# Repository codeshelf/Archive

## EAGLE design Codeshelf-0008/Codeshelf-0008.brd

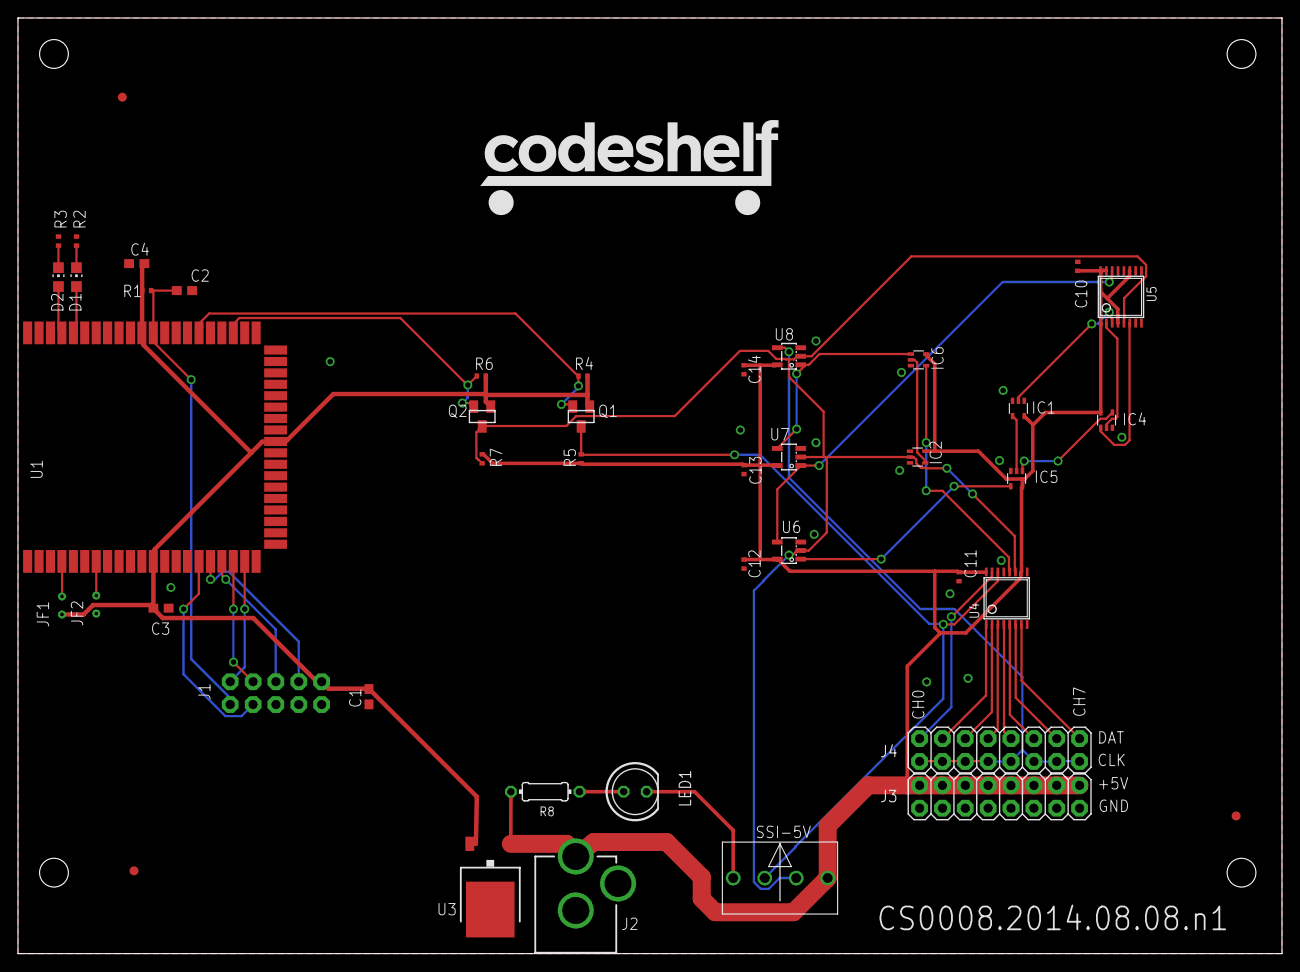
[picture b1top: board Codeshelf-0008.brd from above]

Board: 2 copper layers, 140.5 x 104.0 mm, 45 parts (1 on the bottom side), 39 nets.

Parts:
C1, C3, C4: 100pF; C0603
C2: 1nF; C0603
C10, C11, C12, C13, C14: .1uF; C0402
D1: RED; CHIP-LED0805
D2: GREEN; CHIP-LED0805
IC1, IC2: 74AHC1G04DCK; SC70-5
IC4, IC5, IC6: 74AHC1G08DCK; SC70-5
J1: M05X2PTH; AVR_ICSP
J2: POWER_JACKPTH; POWER_JACK_PTH
J3, J4: M08X2; 2X8
JF1, JF2: JUMPER-2X-SMT-VIA; JUMPER-VIA-2X
LED1: BLUE; LED5MM
Q1, Q2: MOSFET-NCHANNELBSS138; SOT23
R1: 100K; RF-R0402
R2: 220; RF-R0402
R3: 390; RF-R0402
R4, R5, R6, R7: 10K; RF-R0402
R8: 1K; 0204/7
SSI-5V: HEADER-4X39357; MOLEX-39357-0004
U1: ZSFM201-1A; ZSFM201-1
U3: LM2936DT-3.3; TO252
U4: SN74HC595PW; TSSOP16
U5: 74HCT193PW; TSSOP16
U6, U7, U8: D-FLIP-FLOP-74LV1G79DBVR; SOT23-5
U$1: CODESHELF-LOGO
U$2, U$3, U$4: FIDUCIAL; FIDUCIAL_1MM

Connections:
+3V3: C1.1, C3.2, C4.2, J1.9, JF1.1, Q1.1, Q2.1, R1.2, R4.1, R6.1, U1.12, U1.31, U1.50, U3.2
+5V: C10.1, C11.2, C12.2, C13.2, C14.2, IC1.5, IC2.5, IC4.5, IC5.5, IC6.5, J2.PWR, J3.1, J3.3, J3.5, J3.7, J3.9, J3.11, J3.13, J3.15, R5.1, R7.1, R8.2, SSI-5V.4, U3.1, U4.10, U4.16, U5.1, U5.4, U5.11, U5.15, U5.16, U6.5, U7.5, U8.5
GND: C1.2, C2.2, C3.1, C4.1, C10.2, C11.1, C12.1, C13.1, C14.1, IC1.3, IC2.3, IC4.3, IC5.3, IC6.3, J1.10, J2.GND, J2.GNDBREAK, J3.2, J3.4, J3.6, J3.8, J3.10, J3.12, J3.14, J3.16, JF2.1, LED1.K, R2.1, R3.1, SSI-5V.1, U1.1, U1.2, U1.3, U1.22, U1.38, U1.51, U1.58, U1.59, U1.60, U3.3, U4.8, U4.13, U5.8, U6.3, U7.3, U8.3
unnamed: D2.A, U1.57
unnamed: D1.A, U1.56
unnamed: D2.C, R3.2
unnamed: D1.C, R2.2
unnamed: LED1.A, R8.1
unnamed: JF2.2, U1.7
unnamed: JF1.2, U1.4
unnamed: J4.13, U4.1
unnamed: J4.11, U4.2
unnamed: J4.9, U4.3
unnamed: J4.7, U4.4
unnamed: J4.5, U4.5
unnamed: J4.3, U4.6
unnamed: J4.1, U4.7
unnamed: J4.15, U4.15
unnamed: IC1.4, IC5.2
unnamed: IC4.4, IC5.1
unnamed: IC5.4, U6.1
unnamed: U5.14, U6.4, U7.1
unnamed: IC6.1, U7.4, U8.1
unnamed: IC2.4, IC6.2
unnamed: IC1.2, U5.3
unnamed: IC4.2, U5.2
unnamed: IC4.1, U5.6
unnamed: IC6.4, U4.12
RESET: C2.1, J1.2, R1.1, U1.49
RTCK: J1.4, U1.16
SSI-CLK: J4.2, J4.4, J4.6, J4.8, J4.10, J4.12, J4.14, J4.16, U8.4
SSI-CLK-3V3: Q2.2, R6.2, U1.42
SSI-CLK-5V: IC2.2, Q2.3, R7.2, SSI-5V.3, U4.11, U5.5, U6.2, U7.2, U8.2
SSI-TX-3V3: Q1.2, R4.2, U1.45
SSI-TX-5V: Q1.3, R5.2, SSI-5V.2, U4.14
TCK: J1.3, U1.19
TDI: J1.5, U1.18
TDO: J1.7, U1.17
TMS: J1.1, U1.20

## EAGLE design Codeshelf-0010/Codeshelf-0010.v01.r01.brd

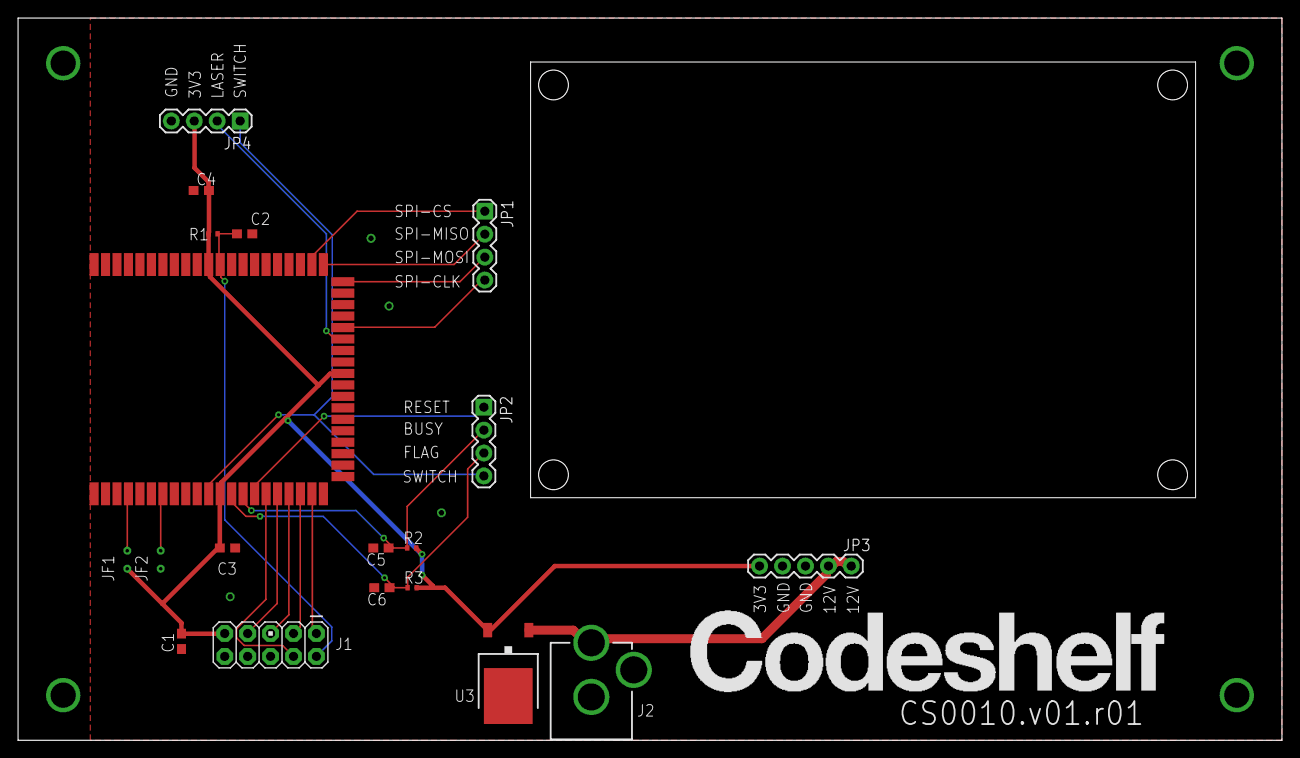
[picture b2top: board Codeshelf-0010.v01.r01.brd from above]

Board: 2 copper layers, 140.0 x 80.0 mm, 21 parts (0 on the bottom side), 20 nets.

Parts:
C1, C3, C4: 100pF; C0603
C2, C5, C6: 1nF; C0603
J1: M05X2PTH; AVR_ICSP
J2: POWER_JACKPTH; POWER_JACK_PTH
JF1, JF2: JUMPER-2X-SMT-VIA; JUMPER-VIA-2X
JP1, JP2, JP4: 1X04
JP3: 1X05
LOGO: CODESHELF-LOGO
R1, R2, R3: 100K; RF-R0402
U1: ZSFM201-1A; ZSFM201-1
U3: LM2936DT-3.3; TO252
U$1: SPARKFUN-BOB-11611

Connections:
#BUSY: C5.1, JP2.2, R2.1, U1.14
#FLAG: C6.1, JP2.3, R3.1, U1.13
#RESET: JP2.1, U1.15
+3V3: C1.1, C3.2, C4.2, J1.9, JF1.1, JP3.5, JP4.3, R1.2, R2.2, R3.2, U1.12, U1.31, U1.50, U3.2
+12V: J2.PWR, JP3.1, JP3.2, U3.1
GND: C1.2, C2.2, C3.1, C4.1, C5.2, C6.2, J1.10, J2.GND, J2.GNDBREAK, JF2.1, JP3.3, JP3.4, JP4.4, U1.1, U1.2, U1.3, U1.22, U1.38, U1.51, U1.58, U1.59, U1.60, U3.3
LASER: JP4.2, U1.34
unnamed: JF2.2, U1.7
unnamed: JF1.2, U1.4
RESET: C2.1, J1.2, R1.1, U1.49
RTCK: J1.4, U1.16
SPI_CLK: JP1.4, U1.35
SPI_CS: JP1.1, U1.41
SPI_MISO: JP1.2, U1.40
SPI_MOSI: JP1.3, U1.39
SWITCH: JP2.4, JP4.1, U1.11
TCK: J1.3, U1.19
TDI: J1.5, U1.18
TDO: J1.7, U1.17
TMS: J1.1, U1.20

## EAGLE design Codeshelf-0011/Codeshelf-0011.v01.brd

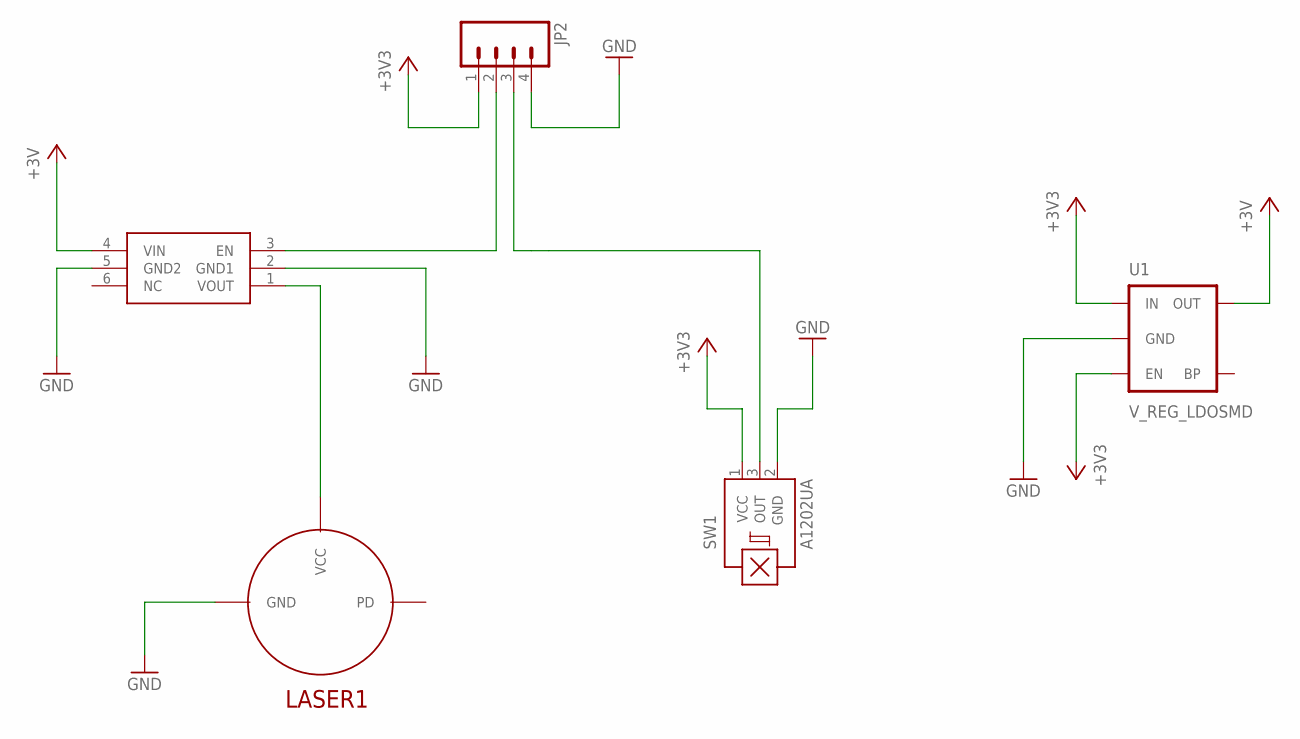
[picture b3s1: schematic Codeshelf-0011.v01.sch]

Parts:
JP2: M04PTH; 1X04
LASER1: LMAPCD-650-06
SW1: A1202UA; SIP3-UA
U1: V_REG_LDOSMD; SOT23-5
U2: MIC94061C6; SC70-6L

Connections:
+3V: U1.5 (OUT), U2.4 (VIN)
+3V3: JP2.1, SW1.1 (VCC), U1.1 (IN), U1.3 (EN)
GND: JP2.4, LASER1.1 (GND), SW1.2 (GND), U1.2 (GND), U2.2 (GND1), U2.5 (GND2)
unnamed: JP2.2, U2.3 (EN)
unnamed: JP2.3, SW1.3 (OUT)
VCC: LASER1.2 (VCC), U2.1 (VOUT)

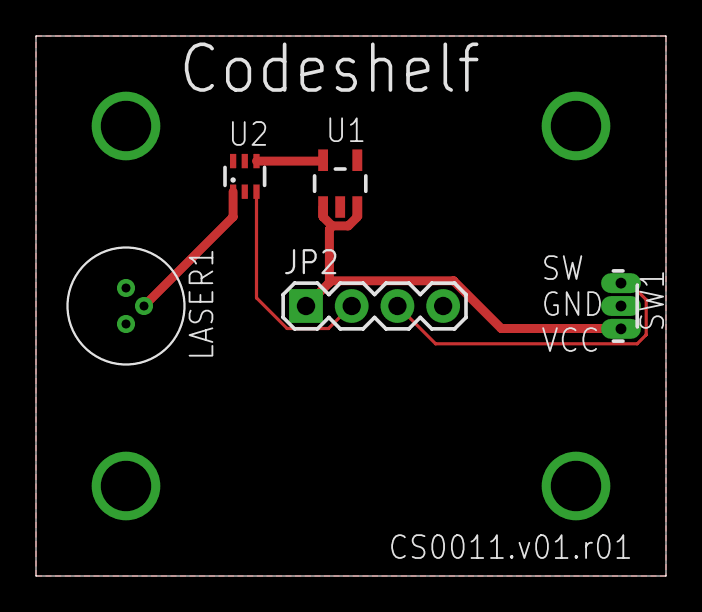
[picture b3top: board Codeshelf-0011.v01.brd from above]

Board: 2 copper layers, 35.0 x 30.0 mm, 5 parts (0 on the bottom side), 6 nets.

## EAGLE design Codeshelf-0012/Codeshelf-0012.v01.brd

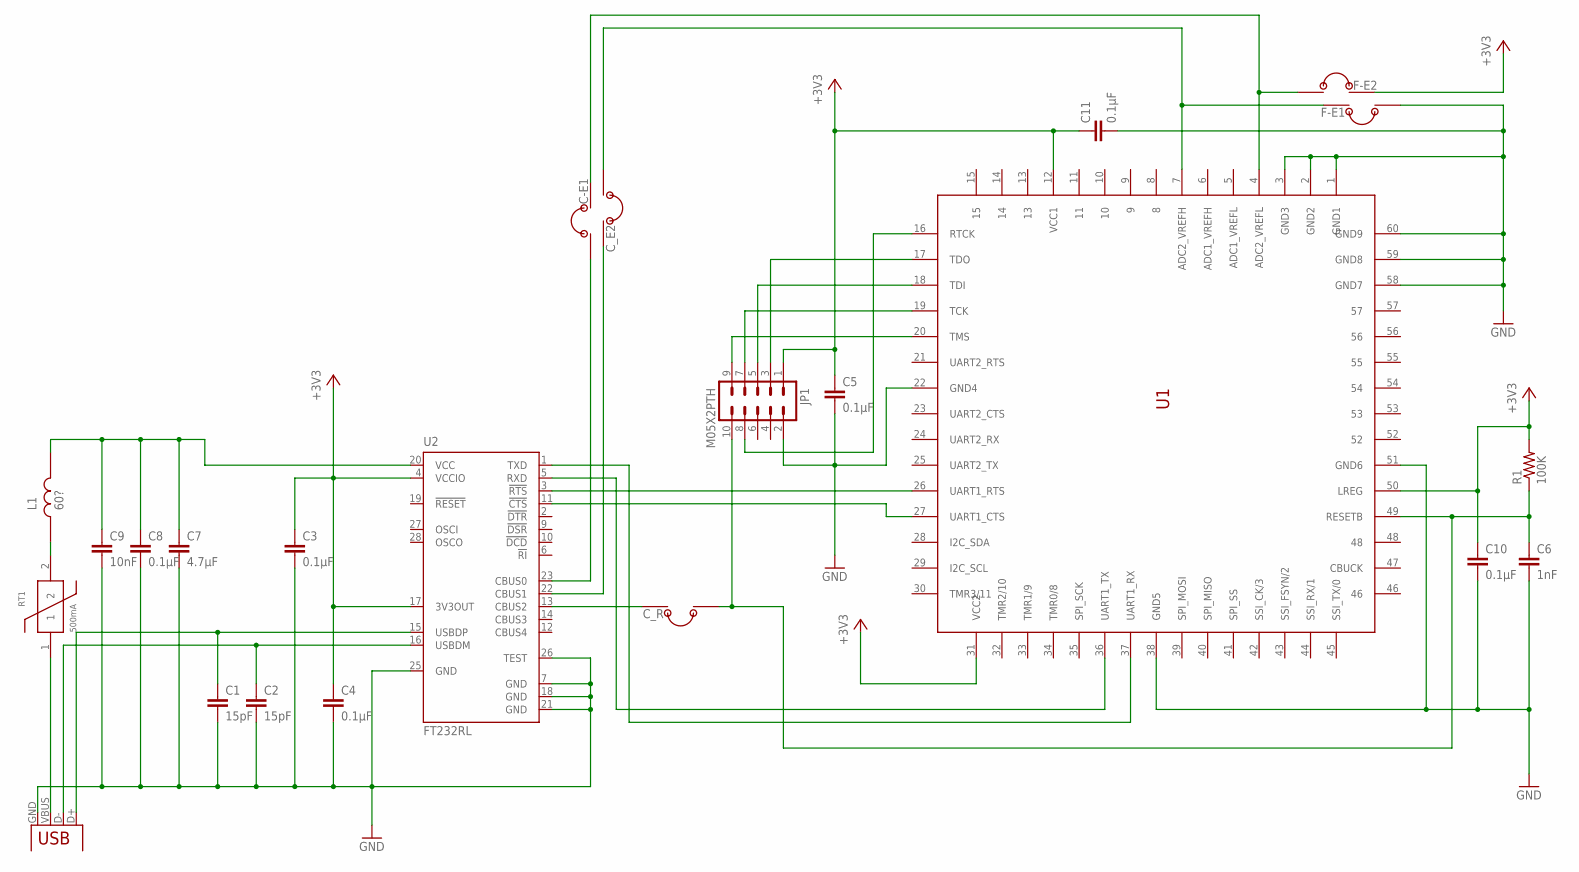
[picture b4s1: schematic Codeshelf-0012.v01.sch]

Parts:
C1, C2: 15pF; C0402
C3, C4, C5, C8, C10, C11: 0.1µF; C0402
C6: 1nF; C0402
C7: 4.7µF; C0805
C9: 10nF; C0402
C-E1: JUMPER-2X-SMT-VIA; JUMPER-VIA-2X
C_E2: JUMPER-2X-SMT-VIA; JUMPER-VIA-2X
C_R: JUMPER-2X-SMT-VIA; JUMPER-VIA-2X
F-E1, F-E2: JUMPER-2X-SMT-VIA; JUMPER-VIA-2X
JP1: M05X2PTH; AVR_ICSP
L1: 60?; RF-L0603
R1: 100K; RF-R0402
RT1: 500mA; C1210
U1: ZSFM201-1A; ZSFM201-1
U2: FT232RL; SSOP28
X1: USBPTH; USB-B-PTH

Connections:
+3V3: C3.1, C4.1, C5.1, C10.1, C11.1, F-E2.2, JP1.1, R1.2, U1.12 (VCC1), U1.31 (VCC2), U1.50 (LREG), U2.4 (VCCIO), U2.17 (3V3OUT)
GND: C1.2, C2.2, C3.2, C4.2, C5.2, C6.2, C7.2, C8.2, C9.2, C10.2, C11.2, F-E1.1, JP1.2, U1.1 (GND1), U1.2 (GND2), U1.3 (GND3), U1.22 (GND4), U1.38 (GND5), U1.51 (GND6), U1.58 (GND7), U1.59 (GND8), U1.60 (GND9), U2.7 (GND), U2.18 (GND), U2.21 (GND), U2.25 (GND), U2.26 (TEST), X1.GND
MCU_CTS: U1.27 (UART1_CTS), U2.11 (!CTS)
MCU_RTS: U1.26 (UART1_RTS), U2.3 (!RTS)
MCU_RX: U1.37 (UART1_RX), U2.1 (TXD)
MCU_TX: U1.36 (UART1_TX), U2.5 (RXD)
unnamed: C-E1.2, F-E2.1, U1.4 (ADC2_VREFL)
unnamed: C_E2.1, F-E1.2, U1.7 (ADC2_VREFH)
unnamed: C-E1.1, U2.23 (CBUS0)
unnamed: C_E2.2, U2.22 (CBUS1)
unnamed: C_R.2, U2.13 (CBUS2)
RESET: C6.1, C_R.1, JP1.10, R1.1, U1.49 (RESETB)
RTCK: JP1.8, U1.16 (RTCK)
TCK: JP1.7, U1.19 (TCK)
TDI: JP1.5, U1.18 (TDI)
TDO: JP1.3, U1.17 (TDO)
TMS: JP1.9, U1.20 (TMS)
USB+: C1.1, U2.15 (USBDP), X1.D+
USB-: C2.1, U2.16 (USBDM), X1.D-
USB_VCC_1: RT1.1, X1.VBUS
USB_VCC_2: L1.2, RT1.2
USB_VCC_3: C7.1, C8.1, C9.1, L1.1, U2.20 (VCC)

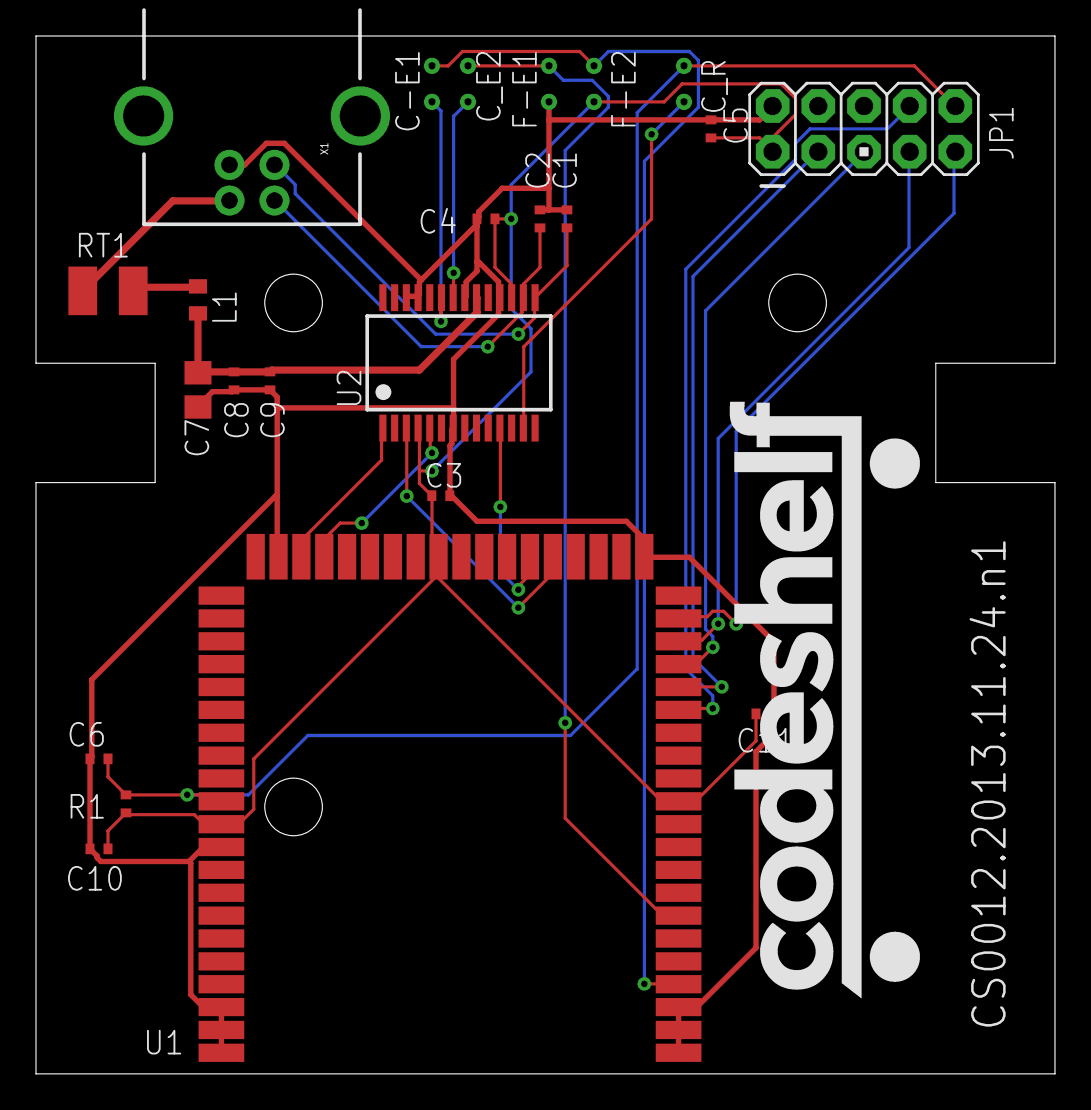
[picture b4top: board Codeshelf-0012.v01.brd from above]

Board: 2 copper layers, 56.6 x 57.7 mm, 24 parts (0 on the bottom side), 22 nets.

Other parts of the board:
U$1: CODESHELF-LOGO

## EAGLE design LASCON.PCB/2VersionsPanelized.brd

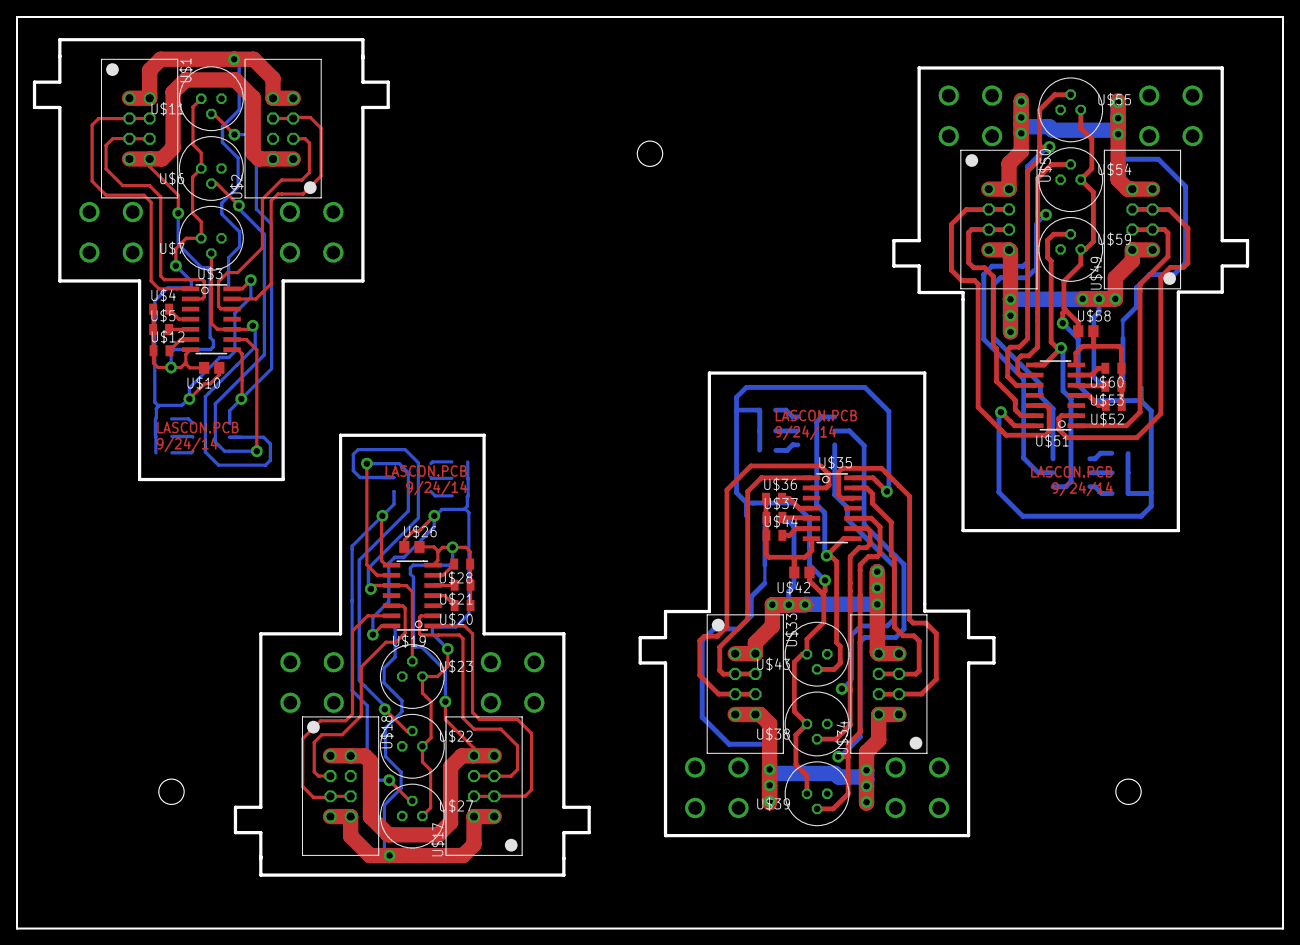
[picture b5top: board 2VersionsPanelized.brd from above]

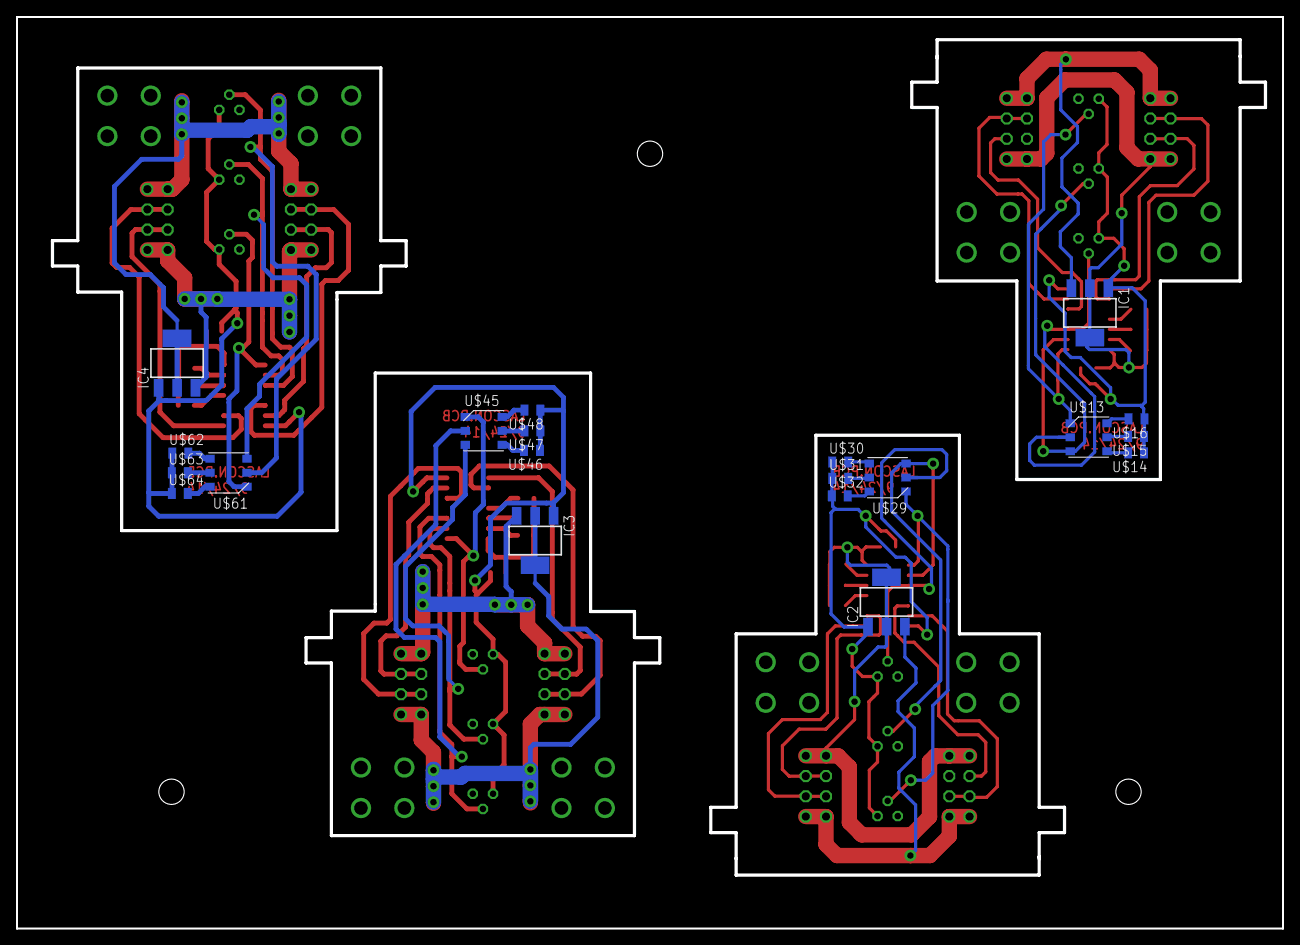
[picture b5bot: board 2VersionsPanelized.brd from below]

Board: 2 copper layers, 158.8 x 114.3 mm, 68 parts (20 on the bottom side), 64 nets.

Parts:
IC1, IC2, IC3, IC4: SOT223
U$1, U$2, U$17, U$18, U$33, U$34, U$49, U$50: 2X4IDC; 2X04
U$3, U$19, U$35, U$51: WS2801; SO14
U$4, U$5, U$12, U$14, U$15, U$16, U$20, U$21, U$28, U$30, U$31, U$32, U$36, U$37, U$44, U$46, U$47, U$48, U$52, U$53, U$60, U$62, U$63, U$64: 24; RF-C0805
U$6, U$7, U$11, U$22, U$23, U$27, U$38, U$39, U$43, U$54, U$55, U$59: LASER
U$8, U$9, U$24, U$25, U$40, U$41, U$56, U$57: 90DEGMNT
U$10, U$26, U$42, U$58: C0805
U$13, U$29, U$45, U$61: LED5060A; PLCC-6

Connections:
+3V1: IC2.1, U$19.14, U$22.1, U$23.1, U$26.1, U$27.1, U$30.1, U$31.1, U$32.1
+3V2: IC3.1, U$35.14, U$38.1, U$39.1, U$42.1, U$43.1, U$46.1, U$47.1, U$48.1
+3V3: IC1.1, U$3.14, U$6.1, U$7.1, U$10.1, U$11.1, U$14.1, U$15.1, U$16.1
+3V4: IC4.1, U$51.14, U$54.1, U$55.1, U$58.1, U$59.1, U$62.1, U$63.1, U$64.1
GND: IC1.2, IC1.4, U$1.7, U$1.8, U$2.1, U$2.2, U$3.7, U$4.1, U$5.1, U$10.2, U$12.1
GND1: IC2.2, IC2.4, U$17.7, U$17.8, U$18.1, U$18.2, U$19.7, U$20.1, U$21.1, U$26.2, U$28.1
GND2: IC3.2, IC3.4, U$33.7, U$33.8, U$34.1, U$34.2, U$35.7, U$36.1, U$37.1, U$42.2, U$44.1
GND3: IC4.2, IC4.4, U$49.7, U$49.8, U$50.1, U$50.2, U$51.7, U$52.1, U$53.1, U$58.2, U$60.1
unnamed: IC1.3, U$1.1, U$1.2, U$2.7, U$2.8
unnamed: U$3.9, U$6.2, U$13.3
unnamed: U$3.10, U$7.2, U$13.2
unnamed: U$3.8, U$11.2, U$13.1
unnamed: U$1.3, U$1.4, U$3.1
unnamed: U$1.5, U$1.6, U$3.2
unnamed: U$2.5, U$2.6, U$3.13
unnamed: U$2.3, U$2.4, U$3.12
unnamed: U$3.4, U$4.2
unnamed: U$3.5, U$5.2
unnamed: U$3.6, U$12.2
unnamed: U$13.4, U$14.2
unnamed: U$13.5, U$15.2
unnamed: U$13.6, U$16.2
unnamed: IC2.3, U$17.1, U$17.2, U$18.7, U$18.8
unnamed: U$17.3, U$17.4, U$19.1
unnamed: U$17.5, U$17.6, U$19.2
unnamed: U$18.5, U$18.6, U$19.13
unnamed: U$18.3, U$18.4, U$19.12
unnamed: U$19.4, U$20.2
unnamed: U$19.5, U$21.2
unnamed: U$19.10, U$23.2, U$29.2
unnamed: U$19.9, U$22.2, U$29.3
unnamed: U$19.8, U$27.2, U$29.1
unnamed: U$19.6, U$28.2
unnamed: U$29.4, U$30.2
unnamed: U$29.5, U$31.2
unnamed: U$29.6, U$32.2
unnamed: IC3.3, U$33.1, U$33.2, U$34.7, U$34.8
unnamed: U$33.3, U$33.4, U$35.1
unnamed: U$33.5, U$33.6, U$35.2
unnamed: U$34.5, U$34.6, U$35.13
unnamed: U$34.3, U$34.4, U$35.12
unnamed: U$35.4, U$36.2
unnamed: U$35.5, U$37.2
unnamed: U$35.10, U$39.2, U$45.2
unnamed: U$35.9, U$38.2, U$45.3
unnamed: U$35.8, U$43.2, U$45.1
unnamed: U$35.6, U$44.2
unnamed: U$45.4, U$46.2
unnamed: U$45.5, U$47.2
unnamed: U$45.6, U$48.2
unnamed: IC4.3, U$49.1, U$49.2, U$50.7, U$50.8
unnamed: U$49.3, U$49.4, U$51.1
unnamed: U$49.5, U$49.6, U$51.2
unnamed: U$50.5, U$50.6, U$51.13
unnamed: U$50.3, U$50.4, U$51.12
unnamed: U$51.4, U$52.2
unnamed: U$51.5, U$53.2
unnamed: U$51.10, U$55.2, U$61.2
unnamed: U$51.9, U$54.2, U$61.3
unnamed: U$51.8, U$59.2, U$61.1
unnamed: U$51.6, U$60.2
unnamed: U$61.4, U$62.2
unnamed: U$61.5, U$63.2
unnamed: U$61.6, U$64.2

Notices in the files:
parts and their libraries:
SparkFun-DiscreteSemi: Licensing: CC v3.0 Share-Alike You are welcome to use this library for commercial purposes.
